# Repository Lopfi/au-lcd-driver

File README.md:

# Alchitry AU LVDS LCD Driver

This is a WIP and doesn't work yet

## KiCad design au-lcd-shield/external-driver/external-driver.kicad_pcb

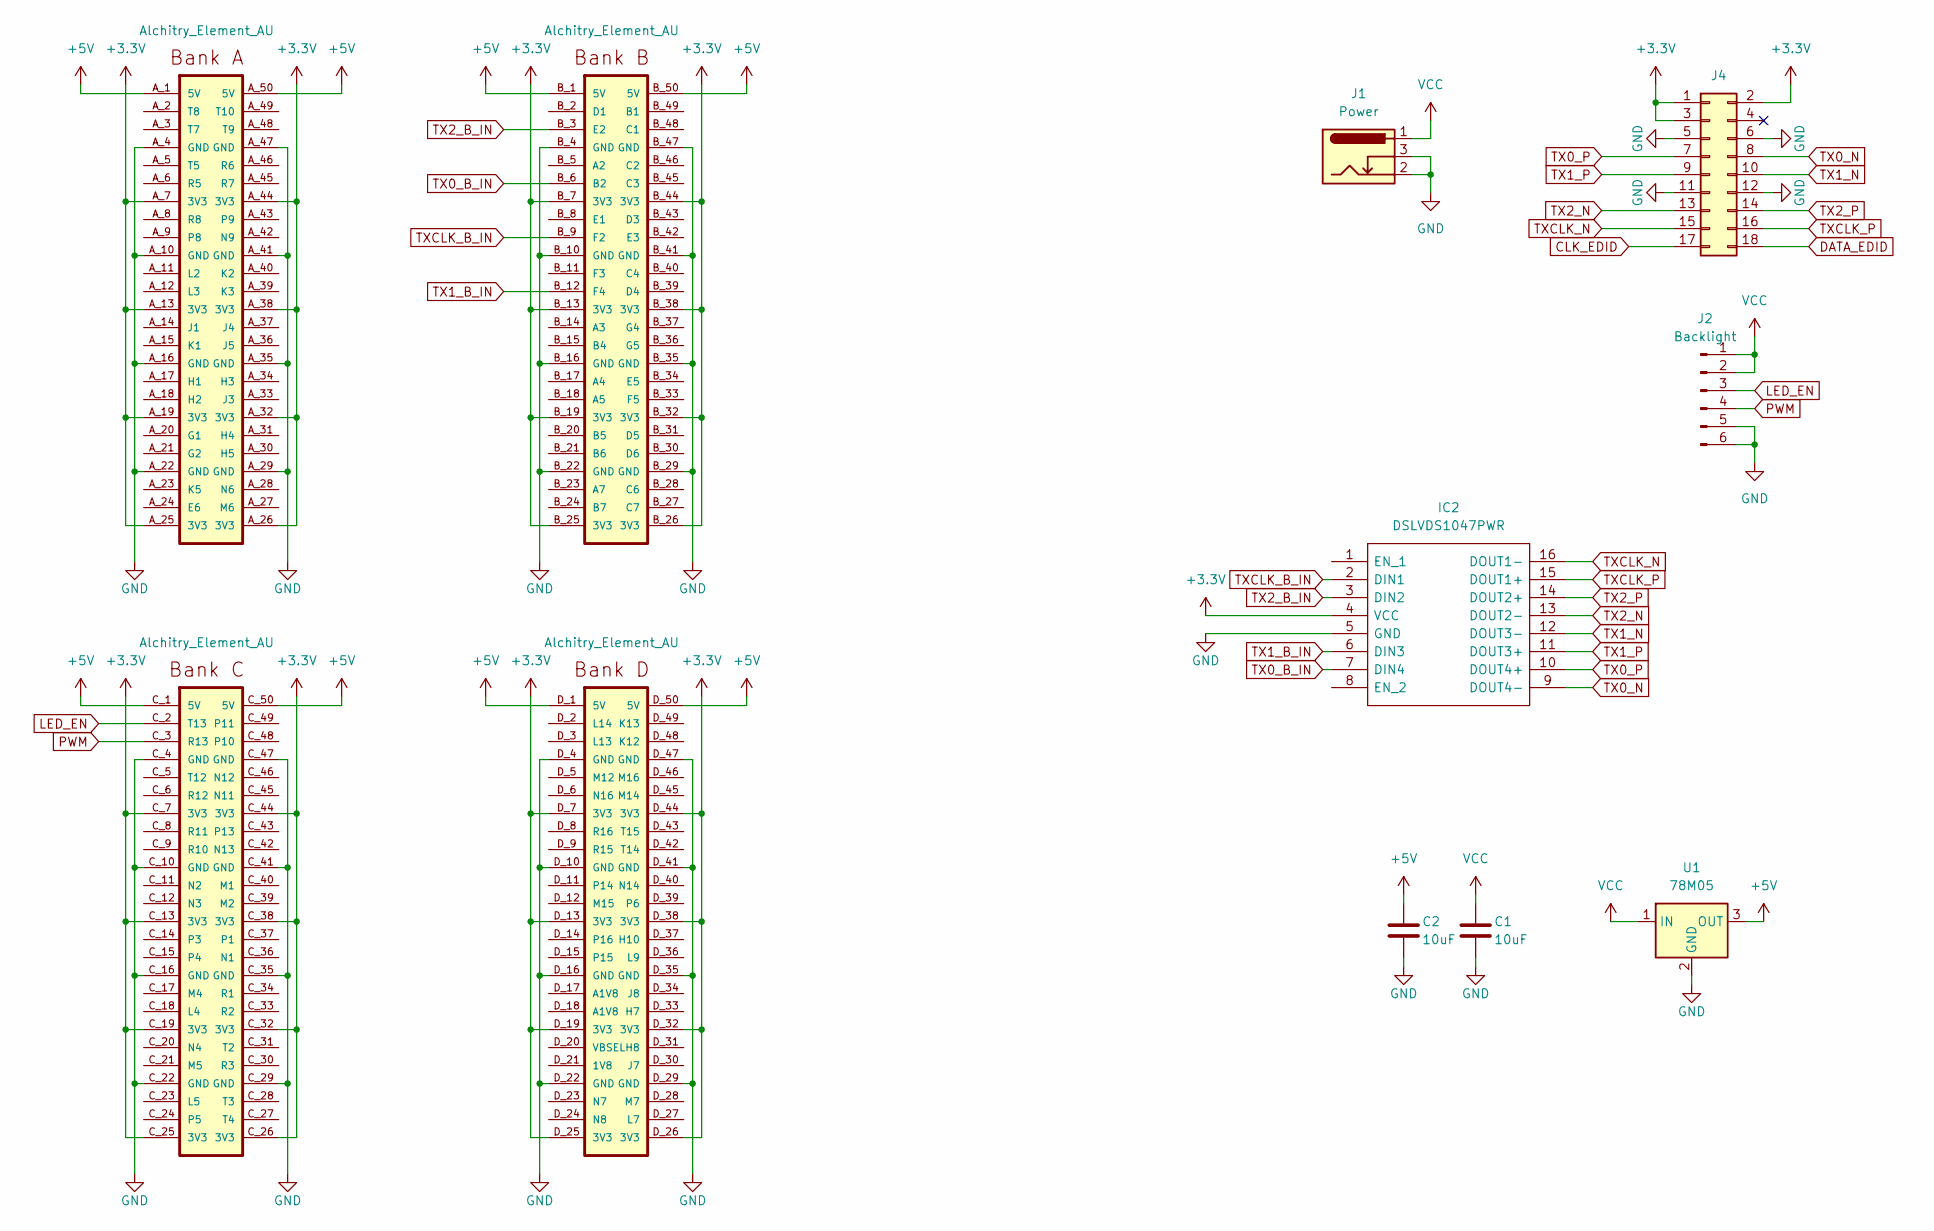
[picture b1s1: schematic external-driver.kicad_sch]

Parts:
B1: Alchitry_Element_AU; Element_no_top
C1, C2: 10uF; C_0603_1608Metric_Pad1.08x0.95mm_HandSolder
IC2: DSLVDS1047PWR; SOP65P640X120-16N; Manufacturer_Part_Number DSLVDS1047PWR; Mouser Part Number 595-DSLVDS1047PWR
J1: Power; TerminalBlock_Phoenix_MKDS-3-2-5.08_1x02_P5.08mm_Horizontal
J2: Backlight; JST_PH_B6B-PH-K_1x06_P2.00mm_Vertical
J4: Conn_02x09_Odd_Even; PinHeader_2x09_P2.00mm_Vertical
U1: 78M05; TO-252-2

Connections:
+3.3V: B1.A_7 (3V3), B1.A_13 (3V3), B1.A_19 (3V3), B1.A_25 (3V3), B1.A_26 (3V3), B1.A_32 (3V3), B1.A_38 (3V3), B1.A_44 (3V3), B1.B_7 (3V3), B1.B_13 (3V3), B1.B_19 (3V3), B1.B_25 (3V3), B1.B_26 (3V3), B1.B_32 (3V3), B1.B_38 (3V3), B1.B_44 (3V3), B1.C_7 (3V3), B1.C_13 (3V3), B1.C_19 (3V3), B1.C_25 (3V3), B1.C_26 (3V3), B1.C_32 (3V3), B1.C_38 (3V3), B1.C_44 (3V3), B1.D_7 (3V3), B1.D_13 (3V3), B1.D_19 (3V3), B1.D_25 (3V3), B1.D_26 (3V3), B1.D_32 (3V3), B1.D_38 (3V3), B1.D_44 (3V3), IC2.4 (VCC), J4.1, J4.2, J4.3
+5V: B1.A_1 (5V), B1.A_50 (5V), B1.B_1 (5V), B1.B_50 (5V), B1.C_1 (5V), B1.C_50 (5V), B1.D_1 (5V), B1.D_50 (5V), C2.2, U1.3 (OUT)
CLK_EDID: J4.17
DATA_EDID: J4.18
GND: B1.A_4 (GND), B1.A_10 (GND), B1.A_16 (GND), B1.A_22 (GND), B1.A_29 (GND), B1.A_35 (GND), B1.A_41 (GND), B1.A_47 (GND), B1.B_4 (GND), B1.B_10 (GND), B1.B_16 (GND), B1.B_22 (GND), B1.B_29 (GND), B1.B_35 (GND), B1.B_41 (GND), B1.B_47 (GND), B1.C_4 (GND), B1.C_10 (GND), B1.C_16 (GND), B1.C_22 (GND), B1.C_29 (GND), B1.C_35 (GND), B1.C_41 (GND), B1.C_47 (GND), B1.D_4 (GND), B1.D_10 (GND), B1.D_16 (GND), B1.D_22 (GND), B1.D_29 (GND), B1.D_35 (GND), B1.D_41 (GND), B1.D_47 (GND), C1.1, C2.1, IC2.5 (GND), J1.2, J1.3, J2.5, J2.6, J4.5, J4.6, J4.11, J4.12, U1.2 (GND)
LED_EN: B1.C_2 (T13), J2.3
PWM: B1.C_3 (R13), J2.4
TX0_B_IN: B1.B_6 (B2), IC2.7 (DIN4)
TX0_N: IC2.9 (DOUT4-), J4.8
TX0_P: IC2.10 (DOUT4+), J4.7
TX1_B_IN: B1.B_12 (F4), IC2.6 (DIN3)
TX1_N: IC2.12 (DOUT3-), J4.10
TX1_P: IC2.11 (DOUT3+), J4.9
TX2_B_IN: B1.B_3 (E2), IC2.3 (DIN2)
TX2_N: IC2.13 (DOUT2-), J4.13
TX2_P: IC2.14 (DOUT2+), J4.14
TXCLK_B_IN: B1.B_9 (F2), IC2.2 (DIN1)
TXCLK_N: IC2.16 (DOUT1-), J4.15
TXCLK_P: IC2.15 (DOUT1+), J4.16
VCC: C1.2, J1.1, J2.1, J2.2, U1.1 (IN)

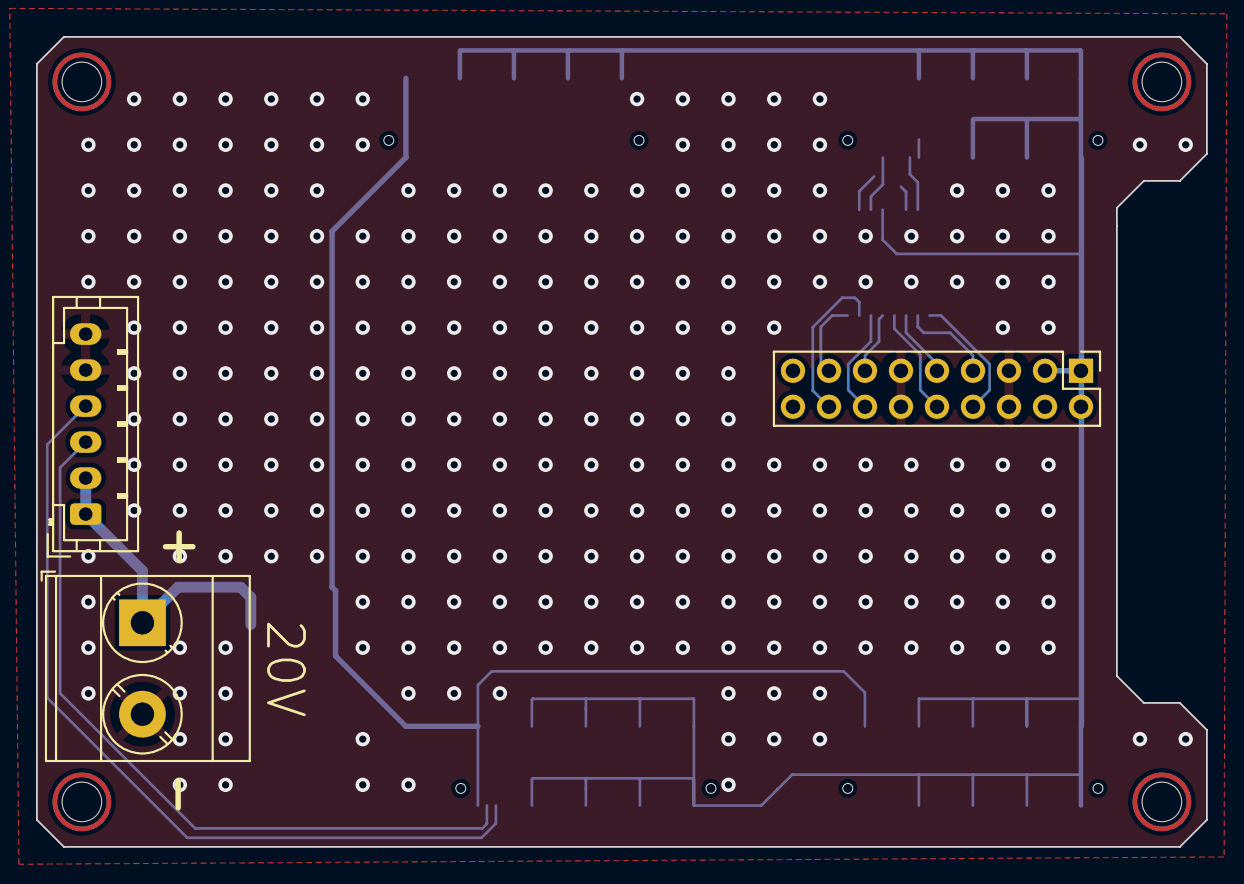
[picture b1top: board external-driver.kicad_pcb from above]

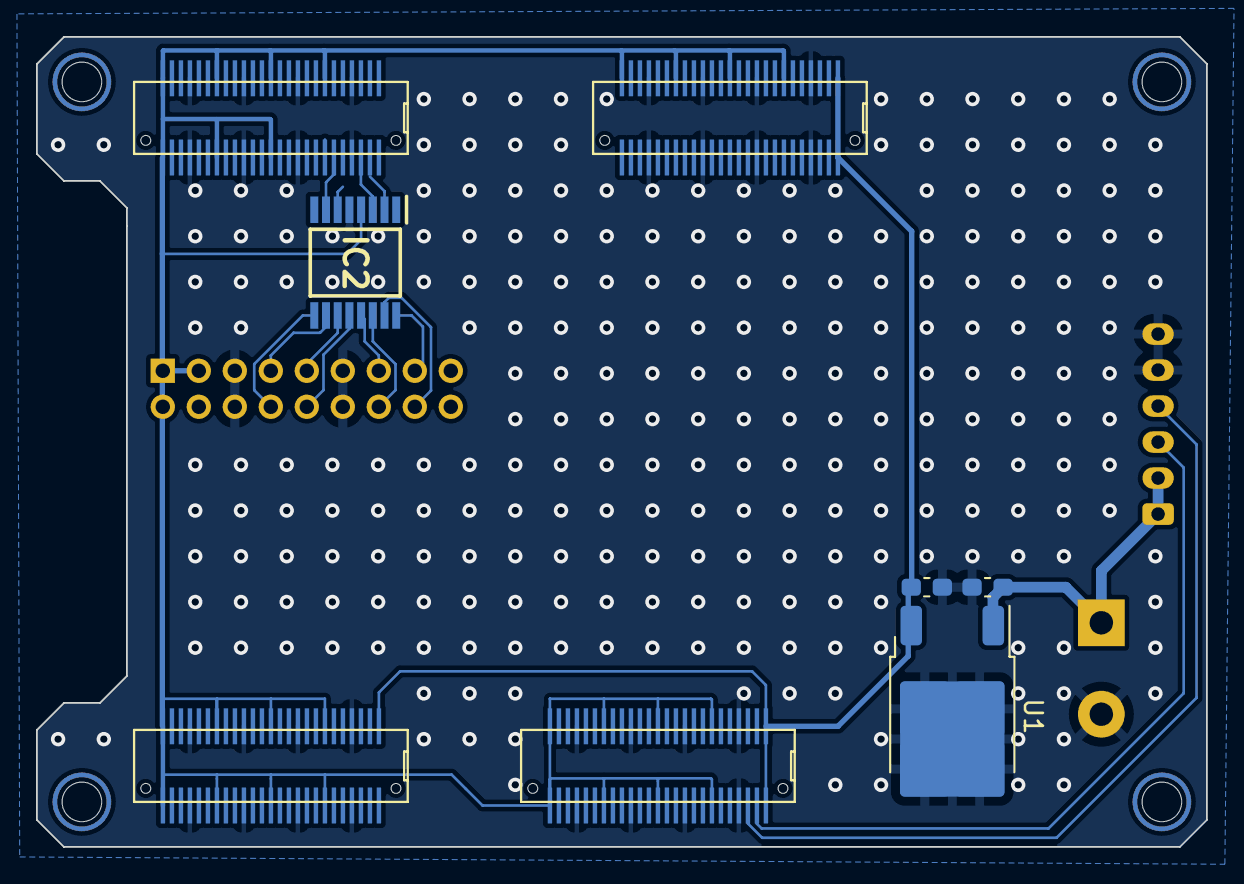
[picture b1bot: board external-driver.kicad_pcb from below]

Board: 2 copper layers, 65.0 x 45.0 mm, 8 parts (4 on the bottom side), 18 nets.

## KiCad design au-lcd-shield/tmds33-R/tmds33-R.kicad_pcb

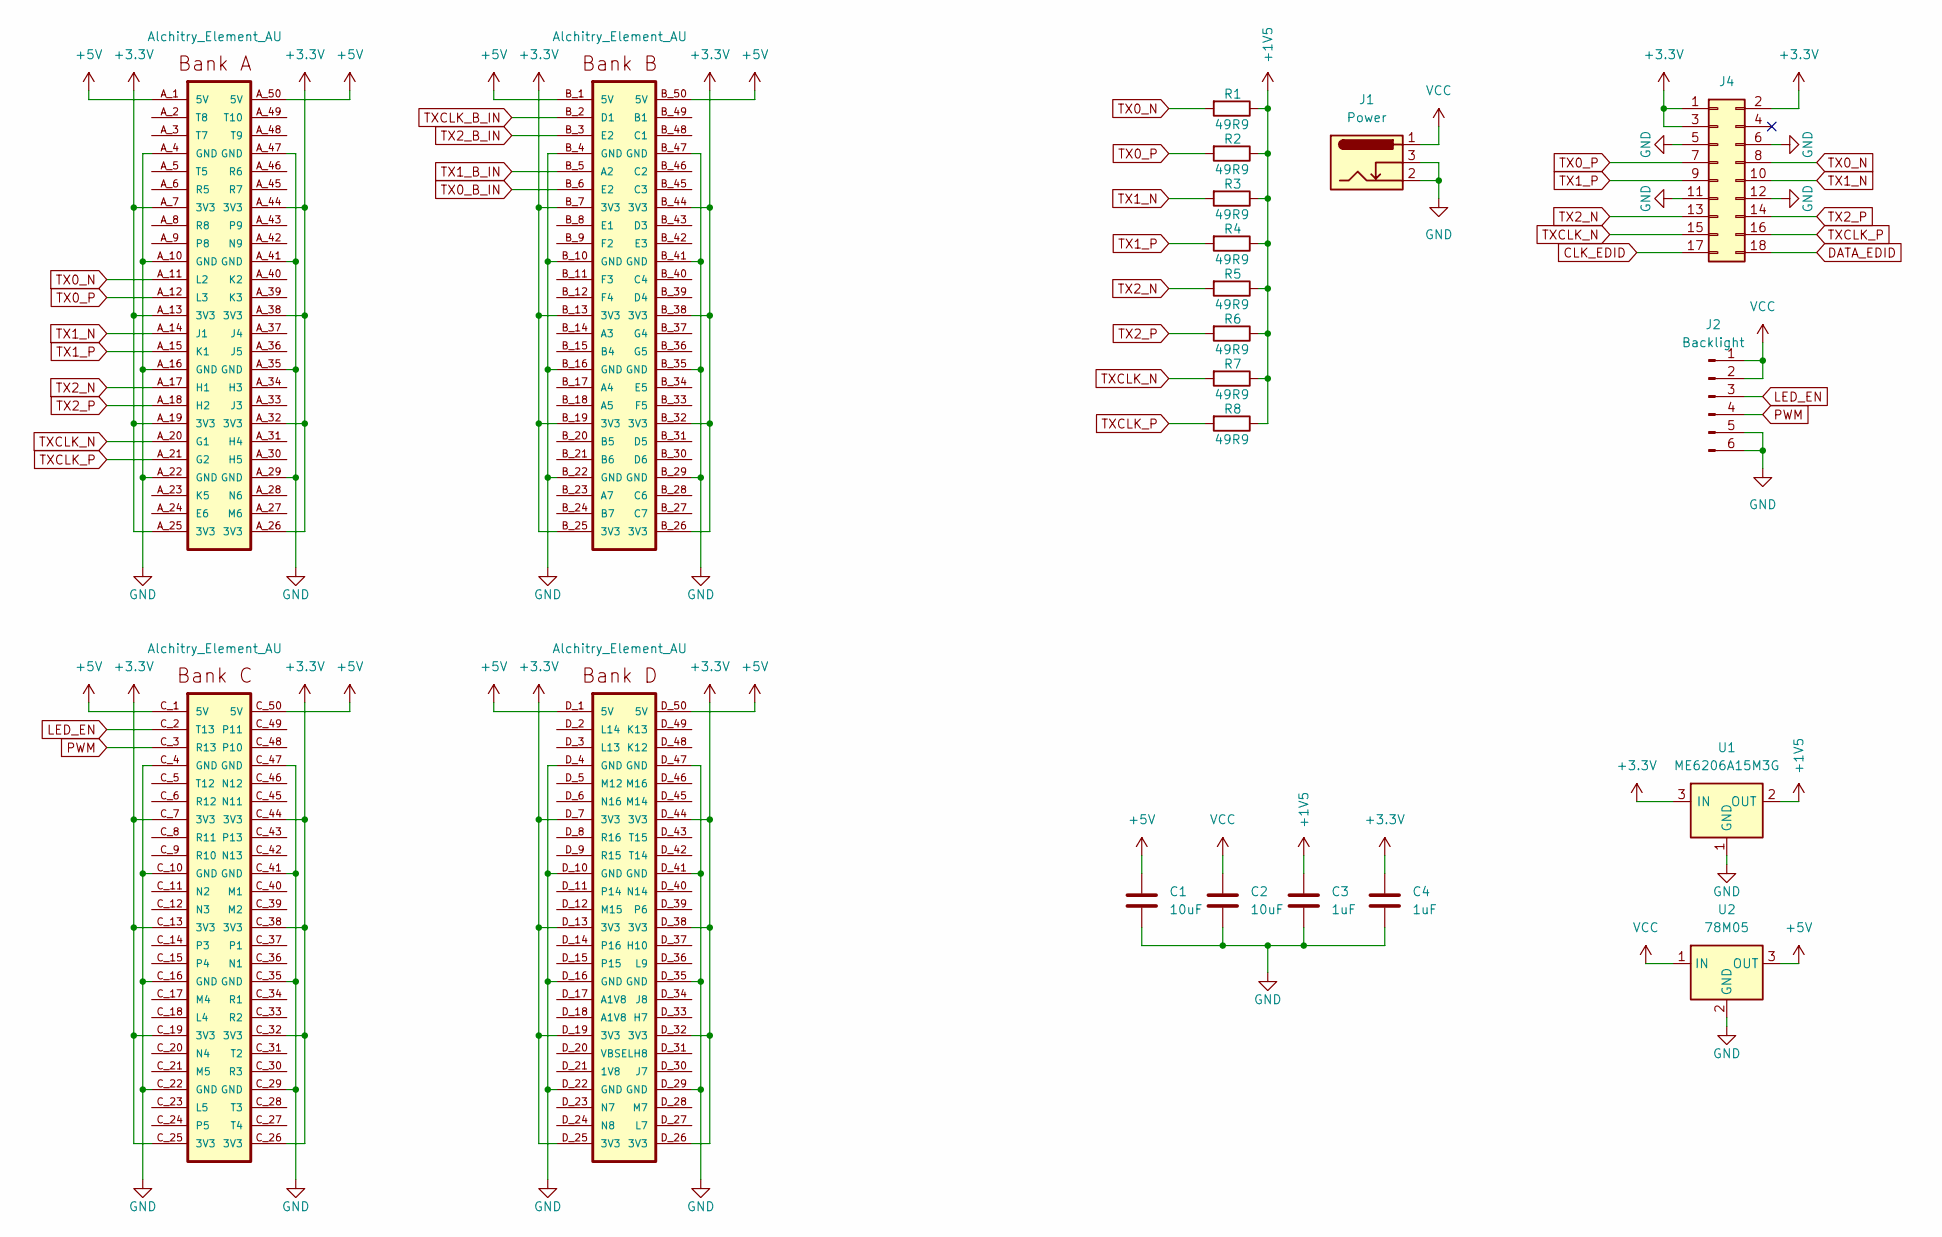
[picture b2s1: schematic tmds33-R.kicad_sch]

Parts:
B1: Alchitry_Element_AU; Element_no_top
C1, C2: 10uF; C_0603_1608Metric_Pad1.08x0.95mm_HandSolder
C3, C4: 1uF; C_0603_1608Metric_Pad1.08x0.95mm_HandSolder
J1: Power; TerminalBlock_Phoenix_MKDS-3-2-5.08_1x02_P5.08mm_Horizontal
J2: Backlight; JST_PH_B6B-PH-K_1x06_P2.00mm_Vertical
J4: Conn_02x09_Odd_Even; PinHeader_2x09_P2.00mm_Vertical
R1, R2, R3, R4, R5, R6, R7, R8: 49R9; R_0603_1608Metric_Pad0.98x0.95mm_HandSolder
U1: ME6206A15M3G; SOT95P285X145-3N; Manufacturer_Part_Number ME6206A15M3G
U2: 78M05; TO-252-2

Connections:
+1V5: C3.1, R1.1, R2.1, R3.1, R4.1, R5.1, R6.1, R7.1, R8.1, U1.2 (OUT)
+3.3V: B1.A_7 (3V3), B1.A_13 (3V3), B1.A_19 (3V3), B1.A_25 (3V3), B1.A_26 (3V3), B1.A_32 (3V3), B1.A_38 (3V3), B1.A_44 (3V3), B1.B_7 (3V3), B1.B_13 (3V3), B1.B_19 (3V3), B1.B_25 (3V3), B1.B_26 (3V3), B1.B_32 (3V3), B1.B_38 (3V3), B1.B_44 (3V3), B1.C_7 (3V3), B1.C_13 (3V3), B1.C_19 (3V3), B1.C_25 (3V3), B1.C_26 (3V3), B1.C_32 (3V3), B1.C_38 (3V3), B1.C_44 (3V3), B1.D_7 (3V3), B1.D_13 (3V3), B1.D_19 (3V3), B1.D_25 (3V3), B1.D_26 (3V3), B1.D_32 (3V3), B1.D_38 (3V3), B1.D_44 (3V3), C4.1, J4.1, J4.2, J4.3, U1.3 (IN)
+5V: B1.A_1 (5V), B1.A_50 (5V), B1.B_1 (5V), B1.B_50 (5V), B1.C_1 (5V), B1.C_50 (5V), B1.D_1 (5V), B1.D_50 (5V), C1.1, U2.3 (OUT)
CLK_EDID: J4.17
DATA_EDID: J4.18
GND: B1.A_4 (GND), B1.A_10 (GND), B1.A_16 (GND), B1.A_22 (GND), B1.A_29 (GND), B1.A_35 (GND), B1.A_41 (GND), B1.A_47 (GND), B1.B_4 (GND), B1.B_10 (GND), B1.B_16 (GND), B1.B_22 (GND), B1.B_29 (GND), B1.B_35 (GND), B1.B_41 (GND), B1.B_47 (GND), B1.C_4 (GND), B1.C_10 (GND), B1.C_16 (GND), B1.C_22 (GND), B1.C_29 (GND), B1.C_35 (GND), B1.C_41 (GND), B1.C_47 (GND), B1.D_4 (GND), B1.D_10 (GND), B1.D_16 (GND), B1.D_22 (GND), B1.D_29 (GND), B1.D_35 (GND), B1.D_41 (GND), B1.D_47 (GND), C1.2, C2.2, C3.2, C4.2, J1.2, J1.3, J2.5, J2.6, J4.5, J4.6, J4.11, J4.12, U1.1 (GND), U2.2 (GND)
LED_EN: B1.C_2 (T13), J2.3
PWM: B1.C_3 (R13), J2.4
TX0_B_IN: B1.B_6 (E2)
TX0_N: B1.A_11 (L2), J4.8, R1.2
TX0_P: B1.A_12 (L3), J4.7, R2.2
TX1_B_IN: B1.B_5 (A2)
TX1_N: B1.A_14 (J1), J4.10, R3.2
TX1_P: B1.A_15 (K1), J4.9, R4.2
TX2_B_IN: B1.B_3 (E2)
TX2_N: B1.A_17 (H1), J4.13, R5.2
TX2_P: B1.A_18 (H2), J4.14, R6.2
TXCLK_B_IN: B1.B_2 (D1)
TXCLK_N: B1.A_20 (G1), J4.15, R7.2
TXCLK_P: B1.A_21 (G2), J4.16, R8.2
VCC: C2.1, J1.1, J2.1, J2.2, U2.1 (IN)

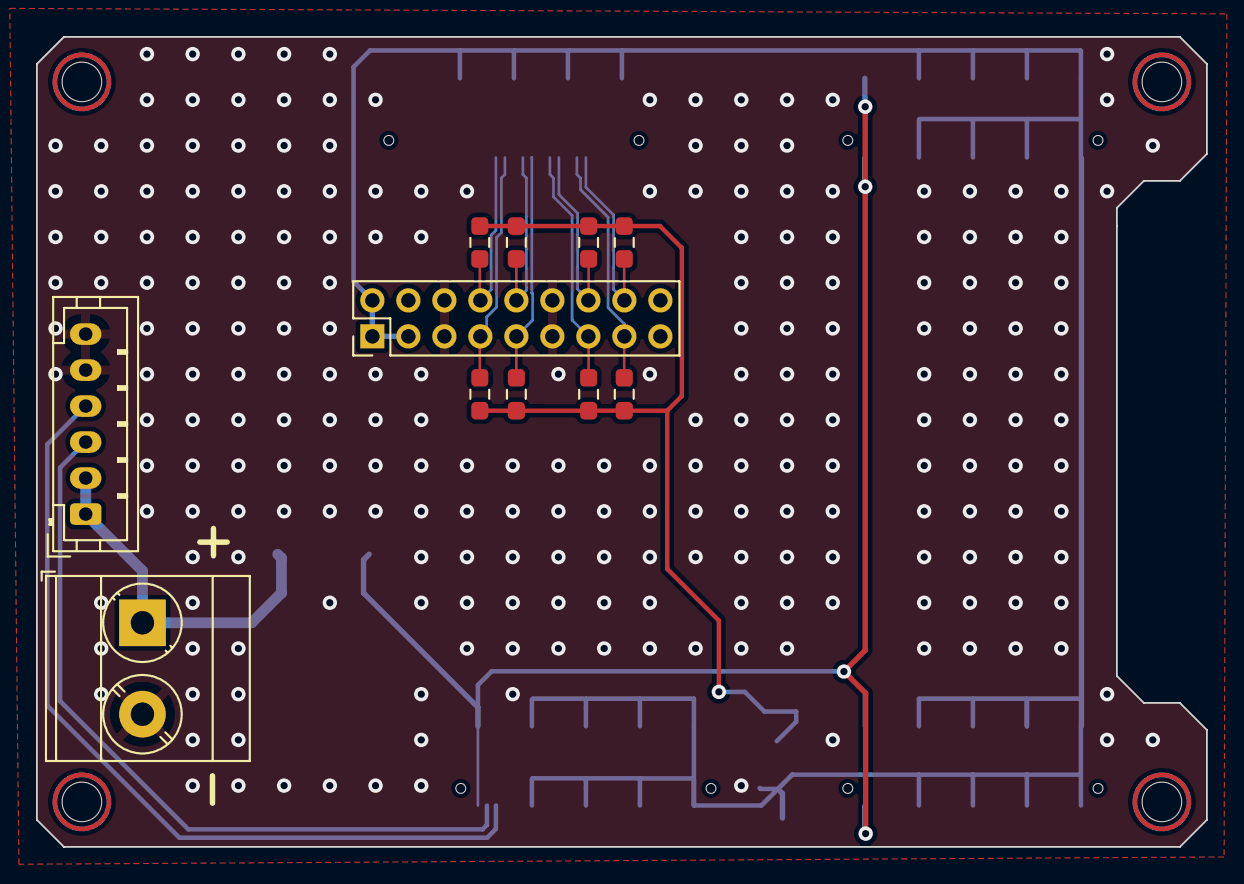
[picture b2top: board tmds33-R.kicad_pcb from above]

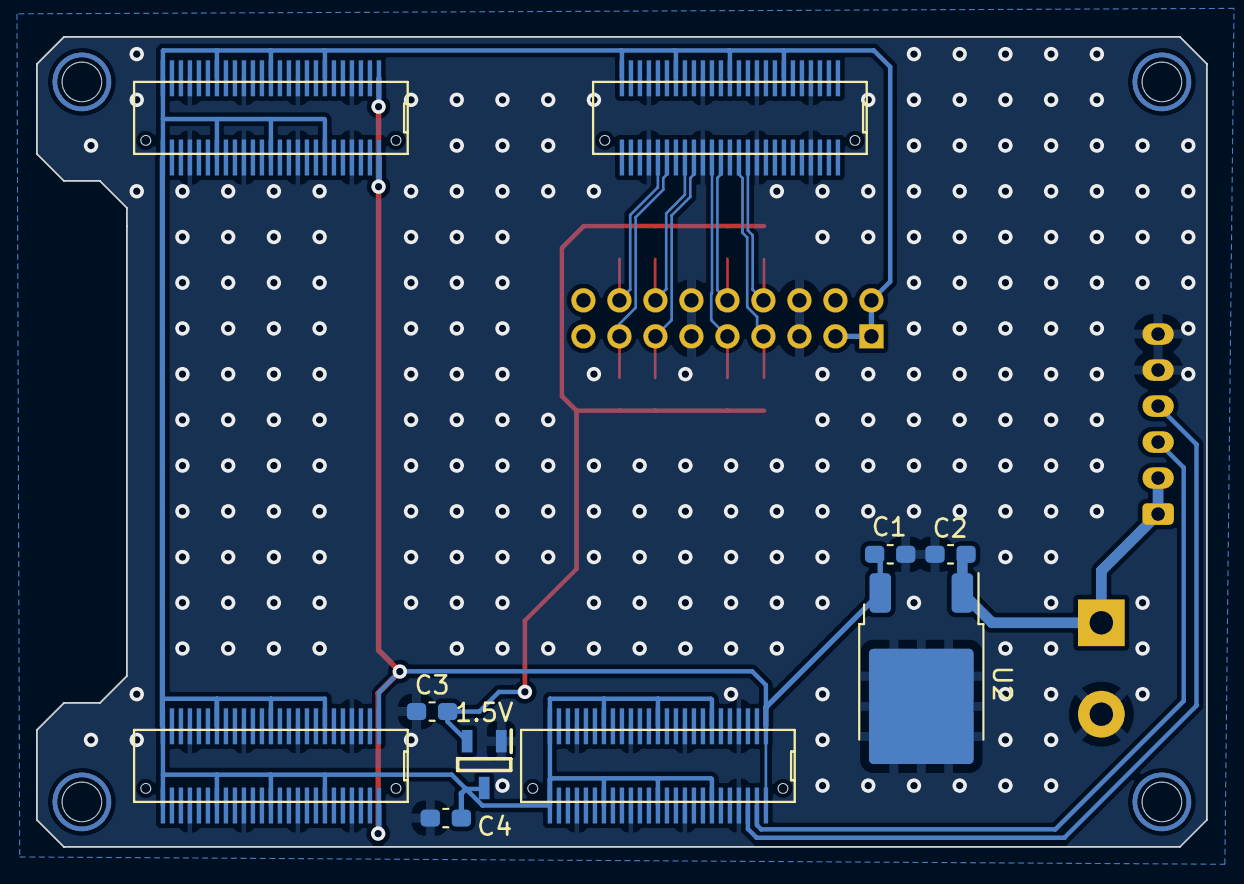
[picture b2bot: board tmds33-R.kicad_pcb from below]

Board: 2 copper layers, 65.0 x 45.0 mm, 18 parts (6 on the bottom side), 15 nets.

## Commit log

2023-10-04 initial
2023-10-09 switch to correct serializer
2023-10-13 fix reset
2023-11-03 add comment for lvds25
2023-11-12 add kicad pcb design
2023-11-12 reroute 3.3v traces
2023-11-12 add lock files to gitignore
2023-11-12 add second pcb version with lvds driver ic
2023-11-12 add filtering caps for ldo's
2023-11-15 minor changes
2023-12-27 pcb v1.0
2024-01-07 rewrite for single ended output to external driver
2024-01-07 fix pins WIP
2025-01-02 add porches
2025-01-03 first time mostly working 26
2025-01-04 try with other display (clock is to fast)
2025-07-29 add debug leds
2025-07-31 only show stripes on upper half of screen
2025-07-31 do some formatting
2025-08-04 minor refractoring
2025-08-04 change porch sizes acording to VESA
2025-08-04 replace cycle generator with assignments
2025-08-04 fixed logic redesign
2025-08-04 update testbench
2025-08-07 getting better results see experiment 36
2025-08-07 only black screen
2025-08-07 fixed screen size, sync and porches but still black screen
